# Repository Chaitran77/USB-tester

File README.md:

My attempt at making  from scratch. It took a while to find a a fully featured USB-C cable, to the point where I was getting a bit concerned that my board was not working, despite my testing it properly. I eventually bought one which worked perfectly.

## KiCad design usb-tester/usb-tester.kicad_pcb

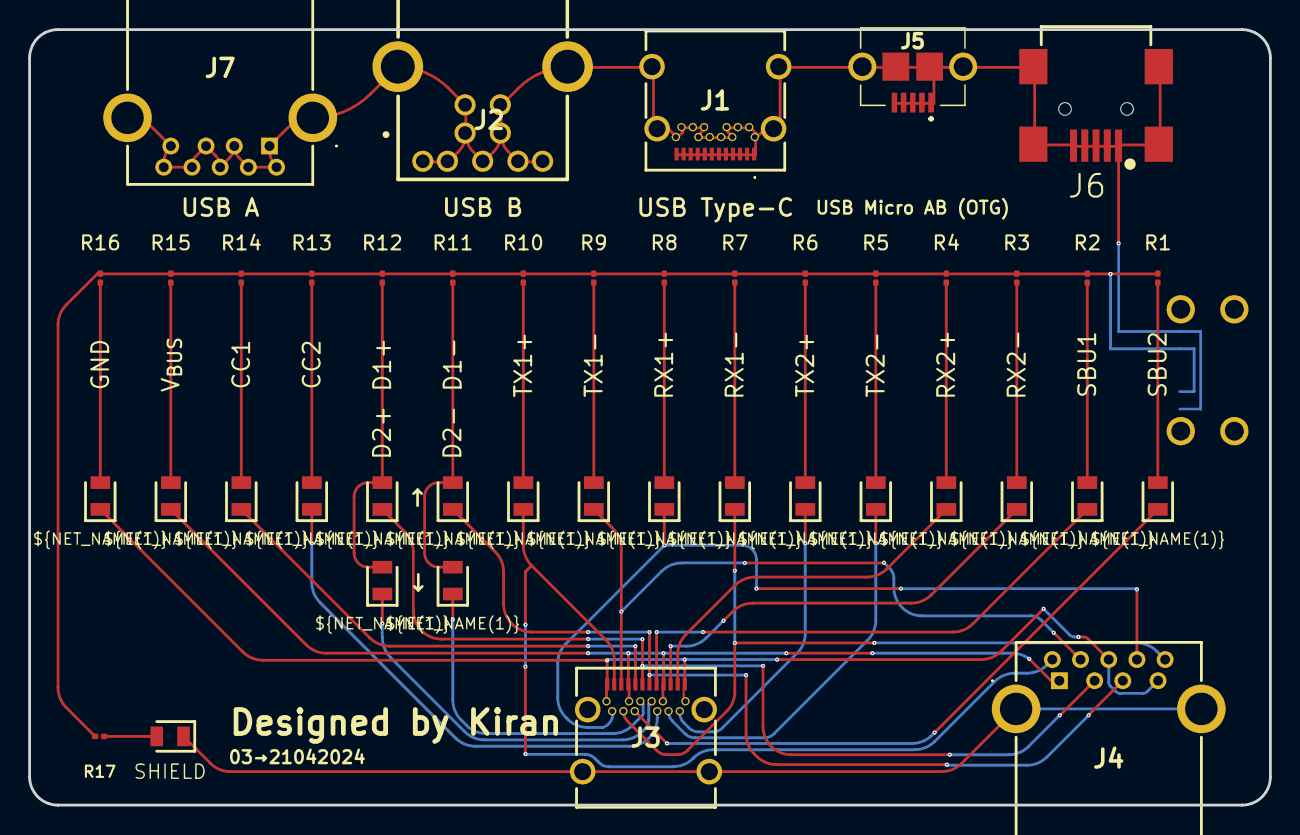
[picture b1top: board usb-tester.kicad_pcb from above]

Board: 2 copper layers, 88.0 x 55.0 mm, 44 parts (1 on the bottom side), 38 nets.

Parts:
J1, J3: USB_C_Receptacle; USB405603A
J2: USB3_B; WR-COM_USB_TYPE_B
J4, J7: USB3_A; USB1135159LB
J5: USB_OTG_MICRO; USB309030A
J6: USB Mini B; GCT_USB2066-05-RBHM-XX-STB-00-01-A_REVD
J8: USB_C_Receptacle_PowerOnly_6P; USB4125GFA
LED1: SBU2; LEDC2012X50N
LED2: SBU1; LEDC2012X50N
LED3: RX2-; LEDC2012X50N
LED4: RX2+; LEDC2012X50N
LED5: TX2-; LEDC2012X50N
LED6: TX2+; LEDC2012X50N
LED7: RX1-; LEDC2012X50N
LED8: RX1+; LEDC2012X50N
LED9: TX1-; LEDC2012X50N
LED10: TX1+; LEDC2012X50N
LED11: D2+; LEDC2012X50N
LED12: D1+; LEDC2012X50N
LED13: CC2; LEDC2012X50N
LED14: CC1; LEDC2012X50N
LED15: V_{BUS}; LEDC2012X50N
LED16: GND; LEDC2012X50N
LED17: D1-; LEDC2012X50N
LED18: D2-; LEDC2012X50N
LED19: SHIELD; LEDC2012X50N
R1, R2, R3, R4, R5, R6, R7, R8, R9, R10, R11, R12, R13, R14, R15, R16, R17: R; R_0201_0603Metric

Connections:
+3V3: J8.A9 (VBUS), J8.B9 (VBUS), R1.2, R2.2, R3.2, R4.2, R5.2, R6.2, R7.2, R8.2, R9.2, R10.2, R11.2, R12.2, R13.2, R14.2, R15.2, R16.2, R17.2
A2: J3.A2 (TX1+), J4.9 (SSTX+), LED10.1 (K)
A3: J3.A3 (TX1-), J4.8 (SSTX-), LED9.1 (K)
A5: J3.A5 (CC1), LED14.1 (K)
A6: J3.A6 (D+), J4.2 (D-), LED12.1 (K)
A7: J3.A7 (D-), J4.3 (D+), LED17.1 (K)
A8: J3.A8 (SBU1), LED2.1 (K)
A10: J3.A10 (RX2-), LED3.1 (K)
A11: J3.A11 (RX2+), LED4.1 (K)
B2: J3.B2 (TX2+), LED6.1 (K)
B3: J3.B3 (TX2-), LED5.1 (K)
B5: J3.B5 (CC2), LED13.1 (K)
B6: J3.B6 (D+), LED11.1 (K)
B7: J3.B7 (D-), LED18.1 (K)
B8: J3.B8 (SBU2), LED1.1 (K)
B10: J3.B10 (RX1-), J4.5 (SSRX-), LED7.1 (K)
B11: J3.B11 (RX1+), J4.6 (SSRX+), LED8.1 (K)
GND: J3.A1 (GND), J3.A12 (GND), J3.B1 (GND), J3.B12 (GND), J4.4 (GND), J4.7 (DRAIN), LED16.1 (K)
GNDPWR: J1.A1 (GND), J1.A2 (TX1+), J1.A3 (TX1-), J1.A4 (VBUS), J1.A5 (CC1), J1.A6 (D+), J1.A7 (D-), J1.A8 (SBU1), J1.A9 (VBUS), J1.A10 (RX2-), J1.A11 (RX2+), J1.A12 (GND), J1.B1 (GND), J1.B2 (TX2+), J1.B3 (TX2-), J1.B4 (VBUS), J1.B5 (CC2), J1.B6 (D+), J1.B7 (D-), J1.B8 (SBU2), J1.B9 (VBUS), J1.B10 (RX1-), J1.B11 (RX1+), J1.B12 (GND), J1.MH1 (SHIELD), J1.MH2 (SHIELD), J1.MH3 (SHIELD), J1.MH4 (SHIELD), J2.1 (VBUS), J2.2 (D-), J2.3 (D+), J2.4 (GND), J2.5 (SSTX-), J2.6 (SSTX+), J2.7 (DRAIN), J2.8 (SSRX-), J2.9 (SSRX+), J2.10 (SHIELD), J2.11 (SHIELD), J5.1 (VBUS), J5.2 (D-), J5.3 (D+), J5.4 (ID), J5.5 (GND), J5.6 (Shield), J5.7 (Shield), J5.8 (Shield), J5.9 (Shield), J6.1 (VBUS), J6.2 (D-), J6.3 (D+), J6.4 (ID), J6.5 (GND), J6.6 (Shield), J6.7 (Shield), J6.8 (Shield), J6.9 (Shield), J7.1 (VBUS), J7.2 (D-), J7.3 (D+), J7.4 (GND), J7.5 (SSRX-), J7.6 (SSRX+), J7.7 (DRAIN), J7.8 (SSTX-), J7.9 (SSTX+), J7.MH1 (SHIELD), J7.MH2 (SHIELD), J8.A12 (GND), J8.B12 (GND)
unnamed: LED1.2 (A), R1.1
unnamed: LED2.2 (A), R2.1
unnamed: LED3.2 (A), R3.1
unnamed: LED4.2 (A), R4.1
unnamed: LED5.2 (A), R5.1
unnamed: LED6.2 (A), R6.1
unnamed: LED7.2 (A), R7.1
unnamed: LED8.2 (A), R8.1
unnamed: LED9.2 (A), R9.1
unnamed: LED10.2 (A), R10.1
unnamed: LED11.2 (A), LED12.2 (A), R12.1
unnamed: LED13.2 (A), R13.1
unnamed: LED14.2 (A), R14.1
unnamed: LED15.2 (A), R15.1
unnamed: LED16.2 (A), R16.1
unnamed: LED17.2 (A), LED18.2 (A), R11.1
unnamed: LED19.2 (A), R17.1
SHIELD: J3.MH3 (SHIELD), J3.MH4 (SHIELD), J4.MH1 (SHIELD), J4.MH2 (SHIELD), LED19.1 (K)
V_{BUS}: J3.A4 (VBUS), J3.A9 (VBUS), J3.B4 (VBUS), J3.B9 (VBUS), J4.1 (VBUS), LED15.1 (K)

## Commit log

2024-04-22 Project tracking initialised
